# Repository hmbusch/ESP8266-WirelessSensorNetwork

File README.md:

# ESP8266-WirelessSensorNetwork
An ESP8266-based environment monitoring solution using wireless sensors and a graphical dashboard.

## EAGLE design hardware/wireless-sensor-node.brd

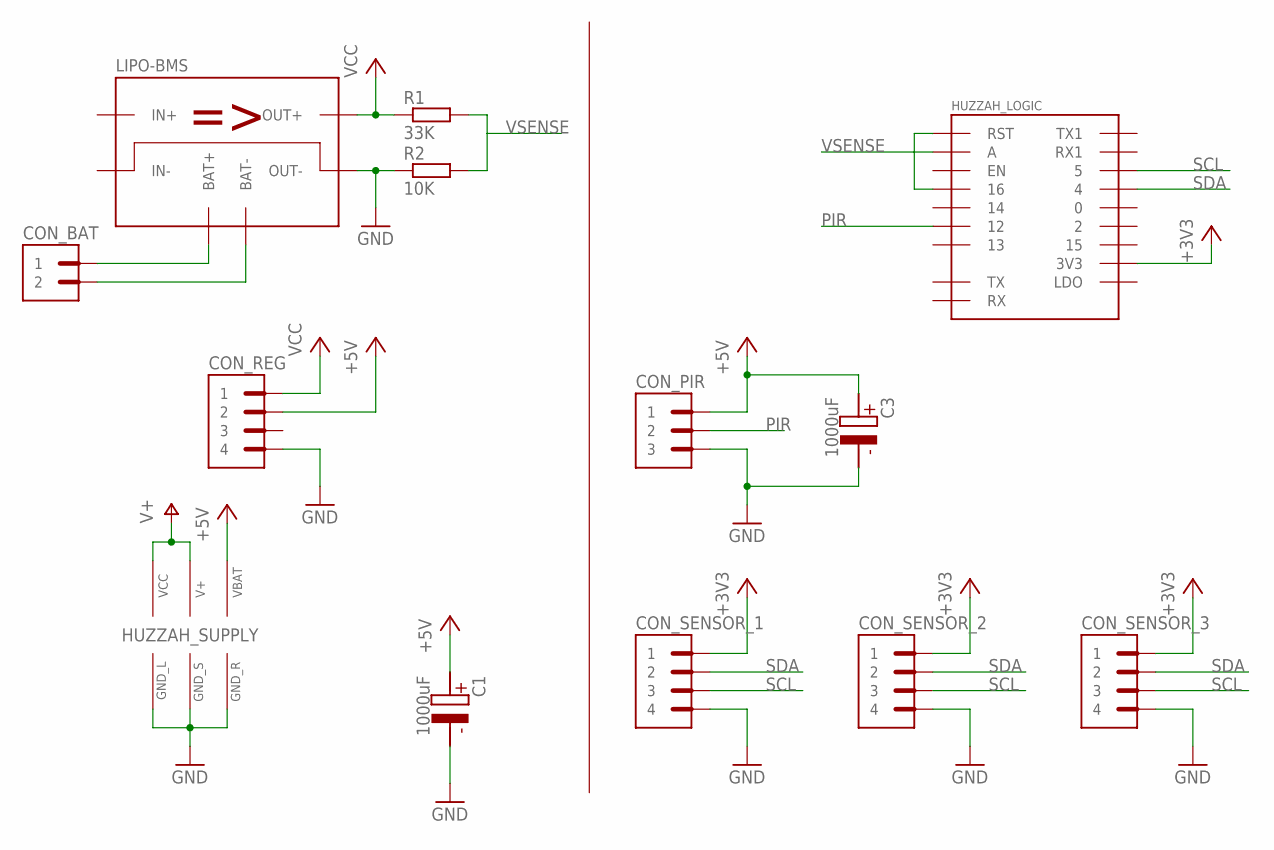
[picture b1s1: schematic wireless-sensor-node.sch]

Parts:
C1, C3: 1000uF; CAP_POL_10X13_5
CON_BAT: PIN_HEADER_2-WIDE; BREAKAWAY_STRAIGHT_2_WIDE
CON_PIR: PIN_HEADER_3-WIDE; BREAKAWAY_STRAIGHT_3_WIDE
CON_REG: PIN_HEADER_4-WIDE; BREAKAWAY_STRAIGHT_4_WIDE
CON_SENSOR_1, CON_SENSOR_2, CON_SENSOR_3: PIN_HEADER_4-WIDE; BREAKAWAY_STRAIGHT_4_WIDE
HUZZAH: ADAFRUIT_HUZZAH-THT-NM; ADAFRUIT_HUZZAH_NO_MOUNTS
LIPO-BMS: LIPO-BMS-CHARGER-MODULE; LIPO-BMS-CHARGER
R1: 33K; RESISTOR-1/4W-AXIAL
R2: 10K; RESISTOR-1/4W-AXIAL

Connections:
+3V3: CON_SENSOR_1.1, CON_SENSOR_2.1, CON_SENSOR_3.1, HUZZAH.3.3V (3V3)
+5V: C1.A, C3.A, CON_PIR.1, CON_REG.2, HUZZAH.VBAT
BAT+: CON_BAT.1, LIPO-BMS.BAT+
BAT-: CON_BAT.2, LIPO-BMS.BAT-
GND: C1.C, C3.C, CON_PIR.3, CON_REG.4, CON_SENSOR_1.4, CON_SENSOR_2.4, CON_SENSOR_3.4, HUZZAH.GND_L, HUZZAH.GND_R, HUZZAH.GND_S, LIPO-BMS.OUT-, R2.P$1 (1)
IN+: LIPO-BMS.IN+
IN-: LIPO-BMS.IN-
unnamed: HUZZAH.16, HUZZAH.RST
PIR: CON_PIR.2, HUZZAH.12
SCL: CON_SENSOR_1.3, CON_SENSOR_2.3, CON_SENSOR_3.3, HUZZAH.5
SDA: CON_SENSOR_1.2, CON_SENSOR_2.2, CON_SENSOR_3.2, HUZZAH.4
V+: HUZZAH.V+, HUZZAH.VCC
VCC: CON_REG.1, LIPO-BMS.OUT+, R1.P$1 (1)
VSENSE: HUZZAH.A, R1.P$2 (2), R2.P$2 (2)

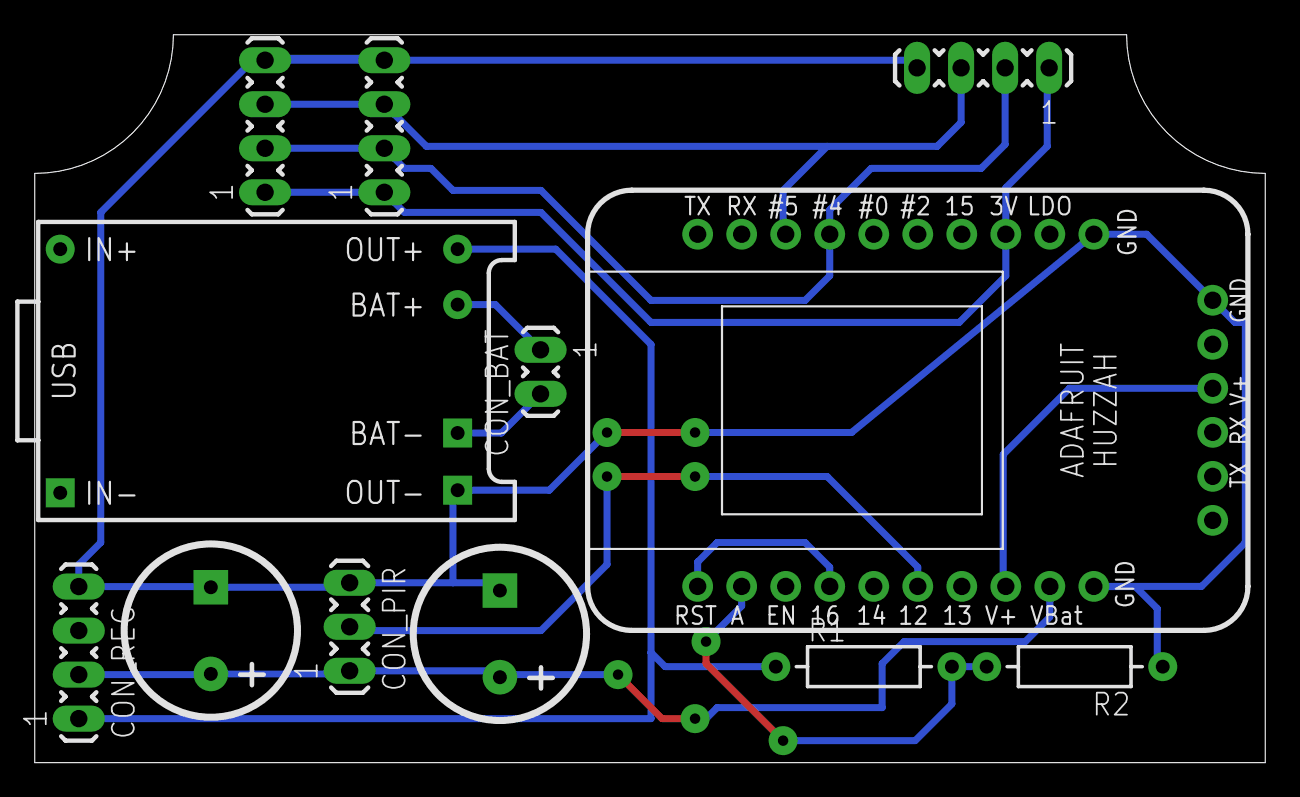
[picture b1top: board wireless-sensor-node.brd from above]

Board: 2 copper layers, 71.0 x 42.0 mm, 12 parts (0 on the bottom side), 12 nets.

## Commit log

2016-07-26 Created circuit and PCB for the sensor with EAGLE
2016-08-14 Created a first skeleton sketch to test REST calls
2016-08-14 Added deep sleep capabilities to the ESP8266 sketch.
    The previously non-existent 'read sensors' step was added
    as a distinct method. It still uses static data, but the
    sketch can already combine and package individual sensor
    readings in to a single JSON document to send to the server.
2016-08-14 The ESP8266 sketch now reads real sensors
    It also transmits real data using three different sensors
    for movement, temperature & humidtity and brightness.
2016-08-15 Sensor data is now sent directly to an InfluxDB
    Why write another time series REST service when
    there are databases like InfluxDB that exactly
    do what we need.
    The sketch was migrated to write to the InfluxDB.
    In addition, a sensor now has a readable ID, which
    allows us to distinguish individual datasets in the
2016-08-15 Added a pressure sensor & static IPs
    In an effort to reduce power consumption by minimizing
    on times, I switched from DHCP to static IP configuration.
    It saves a little time, but still not enough to realize
    decent battery life (I run a sensor node on a single 18650
    lithium ion cell). I still have to tweak the code, but this
    is at least a first step.
2016-08-15 Improved battery life with better connection handling
    Turns out the key to reducing the on time of the sketch
    was to not configure the ESPs network settings when they
    were already configured. This configuration process
    accounted for 50-60% of the total runtime. Now, the ESP
    is only configured when it's SSID differs from the
    configured one. In addition, disconnecting from the
2016-08-15 Added a voltage detection to the sketch
    With an appropriate voltage divider, the sketch can now
    determine and log the current battery voltage.
2016-08-15 Optional pressure readings, better battery voltage
    When deployed in a homestead, it doesn't make sense to equip
    each node with a pressure sensor because the air pressure will
    not vary in such a small area. To accomodate nodes without
    pressure sensors, the sensor can be enabled or disabled via the
    settings file.
    The battery voltage is now read several times and the average value
2016-09-15 Added support for the BME280 sensor
    You can now select which sensors to use by commenting/uncommenting
    their definition in the settings. You cannot enable more than one
    sensor for a given indicator, e.g. you can either use the HDC1000
    or the BME280 to measure temperature and humidity but not both.
    Also fixed the static IP address assignment. When reconnecting,
    WiFi is unconfigured in terms of IP, so the proper configuration
2016-09-16 Redesigned the board to accomodate an BME280 sensor
    The BME280 can now directly attach to the top connecor
    (I will have to verify the pinout still, though).
    Also corrected the voltage divider, I had the resistors
    unintentionally the wrong way round (10K -> 33K instead of
    33K -> 10K), thus exposing the analog pin to far higher
    voltages than intended.
2016-09-18 Optimized battery voltage detection
    Also set an explicit BME280 I2C address. The driver default is
    0x77, my sensor from China uses 0x76 by default, so I had to
    specify that.
    Battery voltage calculation is now down outside of the measuring
    loop to reduce the amount of operations and to reduce rouding
    induced inaccuracies.
2016-09-19 Various improvements (see comment for details)
    IP configuration is now done during every run, otherwise DHCP
    would be used for each run after the initial. That also means
    that the static configuration was not working until now. D'oh!
    Allowed enabling/disabling of the PIR sensor. Until I have found
    a pratical solution to suppress the large amount of RF-induced
    false triggerings, I at least want to be able to switch that
2021-06-07 Added first version of Arduino CI workflow
2021-06-07 Hopefully fixed boards url for esp8266 in CI
2021-06-07 Fixed Arduino library names for CI
2021-06-07 Trial and error for correct CI libraries
2021-06-07 Trial and error with CI libraries #2
2021-06-07 Set correct path to sketches for Arduino CI

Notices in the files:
parts and their libraries:
icmi-passive-parts: ICMI Custom Parts for EAGLE by Hendrik Busch is licensed under a Creative Commons
Attribution-NonCommercial-ShareAlike 3.0 Germany License.
